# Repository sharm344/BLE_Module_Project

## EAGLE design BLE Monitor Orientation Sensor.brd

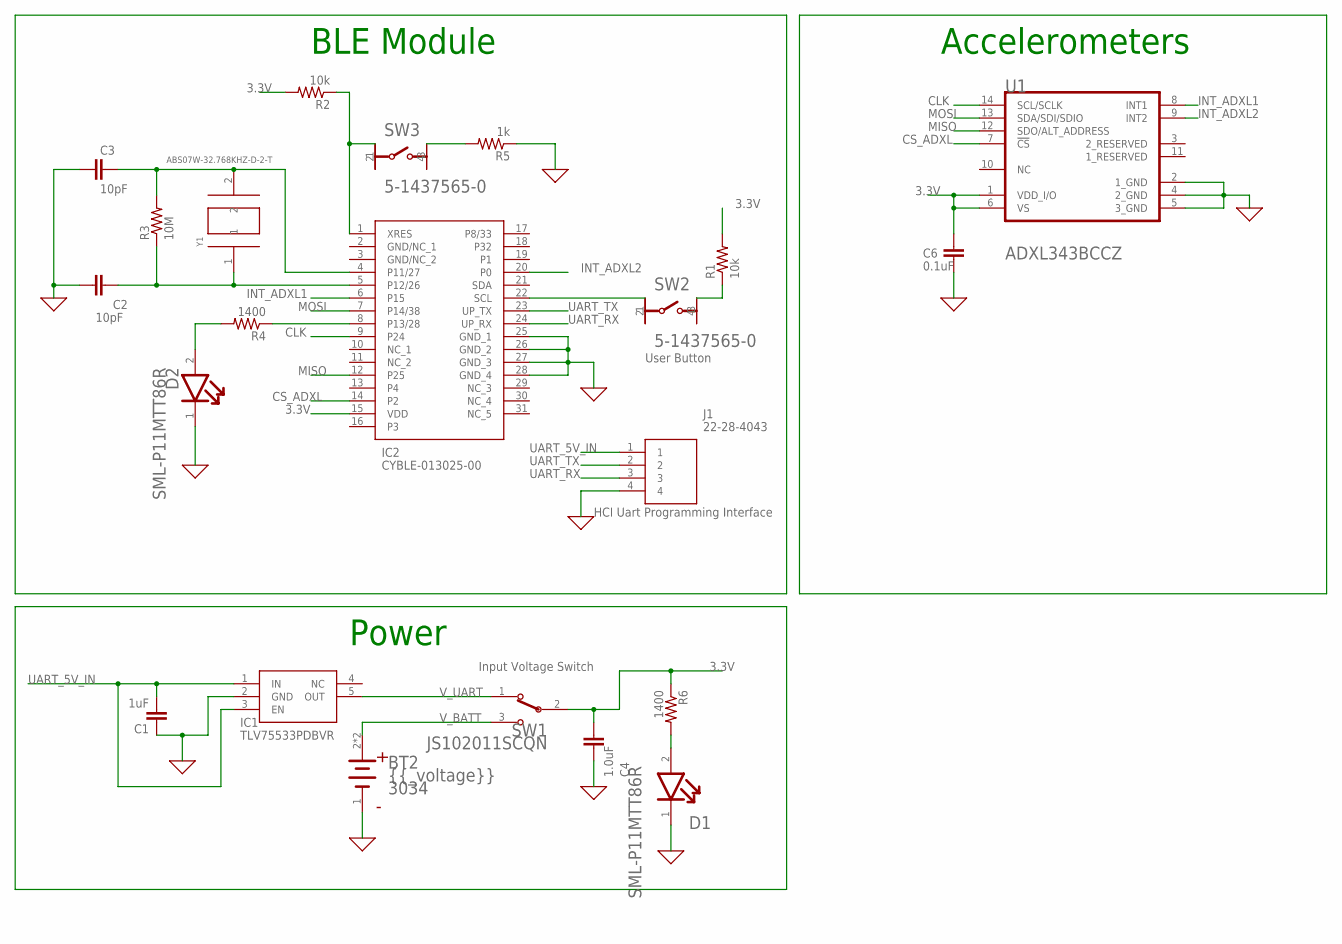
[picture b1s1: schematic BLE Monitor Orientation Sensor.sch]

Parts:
BT2: KEYSTONE_ELECTRONICS_3034KEYSTONE_ELECTRONICS_303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; KEYSTONE_ELECTRONICS_3034_0
C1: 1uF; 0603
C2, C3: 10pF; 0603
C4: 1.0uF; 0603
C6: 0.1uF; 0603
D1, D2: ROHM_SML-P11MTT86RROHM_SML-P11MTT86R_0_0; ROHM_SML-P11MTT86R_0
IC1: TLV75533PDBVR; SOT95P280X145-5N
IC2: CYBLE-013025-00; CYBLE01302500
J1: 22-28-4043; HDRV4W87P0X254_1X4_1016X249X86
R1, R2: 10k; R0603
R3: 10M; R0603
R4, R6: 1400; R0603
R5: 1k; R0603
SW1: C&K_JS102011SCQNC&K_JS102011SCQN_0_0; C&K_JS102011SCQN_0
SW2, SW3: TE_CONNECTIVITY_5-1437565-0TE_CONNECTIVITY_5-1437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; TE_CONNECTIVITY_5-1437565-0_0
U1: ANALOG_DEVICES_ADXL343BCCZANALOG_DEVICES_ADXL343B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; ANALOG_DEVICES_ADXL343BCCZ_0
Y1: ABS07W-32.768KHZ-D-2-T; XTAL320X150X90

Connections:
3.3V: C4.1, C6.2, IC2.15 (VDD), R1.2, R2.2, R6.1, SW1.2, U1.1 (VDD_I/O), U1.6 (VS)
CLK: IC2.9 (P24), U1.14 (SCL/SCLK)
CS_ADXL: IC2.14 (P2), U1.7 (!CS!)
GND: BT2.1 (CATHODE), C1.1, C2.1, C3.1, C4.2, C6.1, D1.1 (CATHODE), D2.1 (CATHODE), IC1.2 (GND), IC2.25 (GND_1), IC2.26 (GND_2), IC2.27 (GND_3), IC2.28 (GND_4), J1.4, R5.1, U1.2 (1_GND), U1.4 (2_GND), U1.5 (3_GND)
INT_ADXL1: IC2.6 (P15), U1.8 (INT1)
INT_ADXL2: IC2.20 (P0), U1.9 (INT2)
MISO: IC2.12 (P25), U1.12 (SDO/ALT_ADDRESS)
MOSI: IC2.7 (P14/38), U1.13 (SDA/SDI/SDIO)
unnamed: R1.1, SW2.3
unnamed: IC2.1 (XRES), R2.1, SW3.1
unnamed: IC2.22 (SCL), SW2.1
unnamed: IC2.8 (P13/28), R4.1
unnamed: D1.2 (ANODE), R6.2
unnamed: D2.2 (ANODE), R4.2
unnamed: R5.2, SW3.3
unnamed: C2.2, IC2.5 (P12/26), R3.1, Y1.1
unnamed: C3.2, IC2.4 (P11/27), R3.2, Y1.2
UART_5V_IN: C1.2, IC1.1 (IN), IC1.3 (EN), J1.1
UART_RX: IC2.24 (UP_RX), J1.3
UART_TX: IC2.23 (UP_TX), J1.2
V_BATT: BT2.2 (ANODE), BT2.2-2 (ANODE), SW1.3
V_UART: IC1.5 (OUT), SW1.1

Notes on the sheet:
BLE Module
Accelerometers
Power

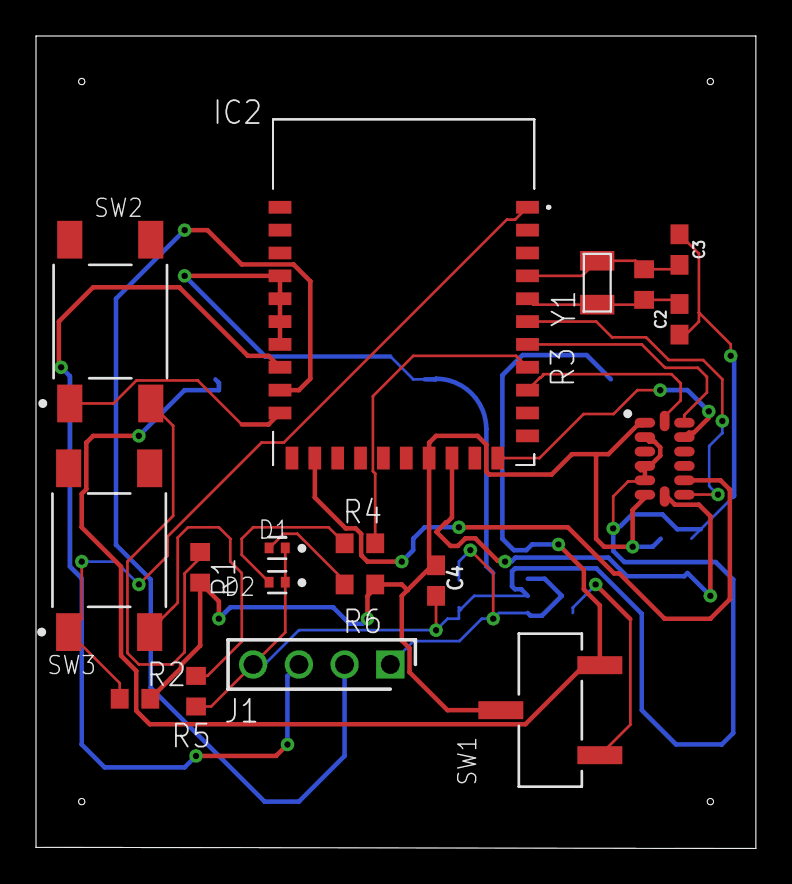
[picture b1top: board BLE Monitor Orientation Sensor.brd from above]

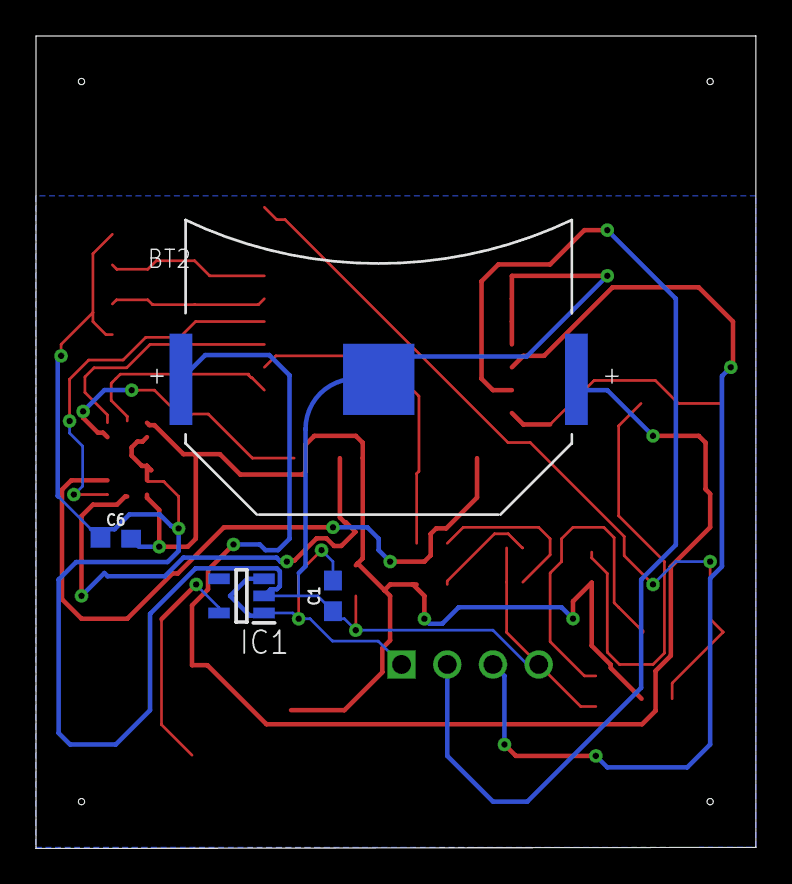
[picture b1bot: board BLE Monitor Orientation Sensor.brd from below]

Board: 2 copper layers, 40.0 x 45.1 mm, 22 parts (4 on the bottom side), 22 nets.

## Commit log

2021-08-30 Revision 1 of Schematic and Board Files

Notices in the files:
parts and their libraries:
SparkFun-Capacitors: Licensing: Creative Commons ShareAlike 4.0 International - https://creativecommons.org/licenses/by-sa/4.0
